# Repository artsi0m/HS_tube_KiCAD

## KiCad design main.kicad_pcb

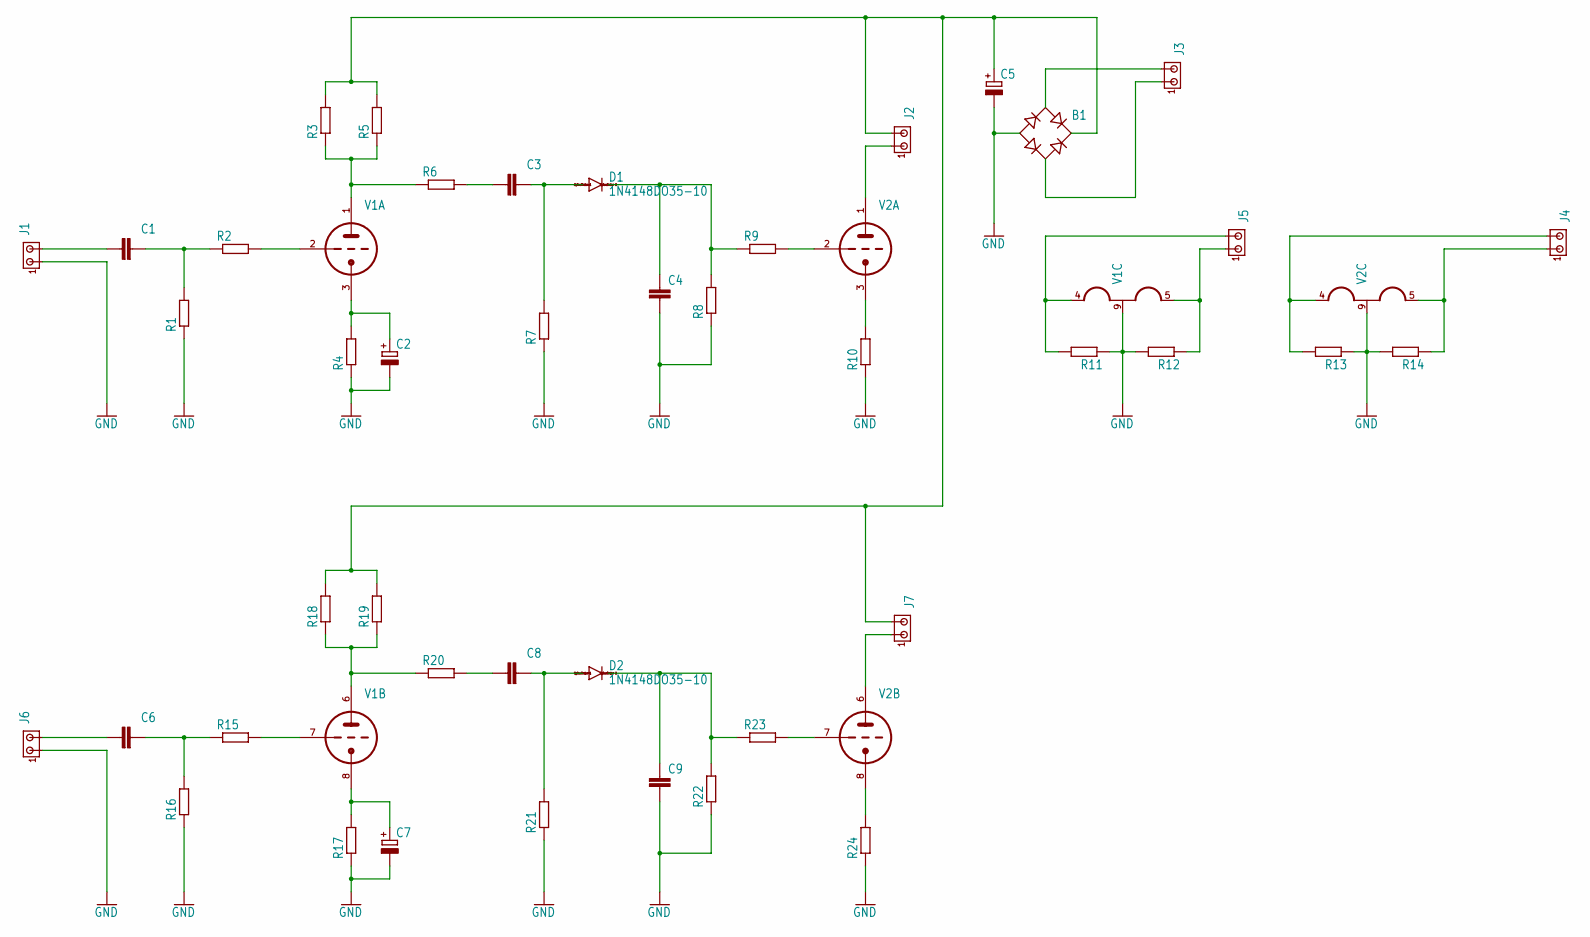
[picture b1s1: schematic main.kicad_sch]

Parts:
B1: B-DIL
C1, C3, C6, C8: C-EU225-062X268; C225-062X268
C2, C7: CPOL-EUE5-10.5; E5-10,5
C4, C9: C-EU102-064X133; C102-064X133
C5: CPOL-EUE7.5-18; E7,5-18
D1, D2: 1N4148DO35-10; DO35-10
J1, J2, J3, J4, J5, J6, J7: MTA02-156; 1X2MTA
R1, R2, R4, R6, R7, R8, R9, R10, R11, R12, R13, R14, R15, R16, R17, R20, R21, R22, R23, R24: R-EU_0207/12; 0207_12
R3, R5, R18, R19: R-EU_0309/12; 0309_12
V1, V2: 12AX7-P; TUBE

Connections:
GND: B1.-, C2.-, C4.2, C5.-, C7.-, C9.2, J1.1, J6.1, R1.1, R4.1, R7.1, R8.1, R10.1, R11.1, R12.2, R13.1, R14.2, R16.1, R17.1, R21.1, R22.1, R24.1, V1.9 (H2), V2.9 (H2)
unnamed: B1.+, C5.+, J2.2, J7.2, R3.2, R5.2, R18.2, R19.2
unnamed: B1.AC1, J3.2
unnamed: B1.AC2, J3.1
unnamed: C1.1, J1.2
unnamed: C1.2, R1.2, R2.1
unnamed: C3.1, R6.2
unnamed: C3.2, D1.A, R7.2
unnamed: C4.1, D1.C, R8.2, R9.1
unnamed: C6.1, J6.2
unnamed: C6.2, R15.1, R16.2
unnamed: C8.1, R20.2
unnamed: C8.2, D2.A, R21.2
unnamed: C9.1, D2.C, R22.2, R23.1
unnamed: R3.1, R5.1, R6.1, V1.1 (TA)
unnamed: R2.2, V1.2 (TG)
unnamed: C2.+, R4.2, V1.3 (TK)
unnamed: R18.1, R19.1, R20.1, V1.6 (TA)
unnamed: R15.2, V1.7 (TG)
unnamed: C7.+, R17.2, V1.8 (TK)
unnamed: J5.2, R11.2, V1.4 (H1)
unnamed: J5.1, R12.1, V1.5 (H3)
unnamed: J2.1, V2.1 (TA)
unnamed: R9.2, V2.2 (TG)
unnamed: R10.2, V2.3 (TK)
unnamed: J7.1, V2.6 (TA)
unnamed: R23.2, V2.7 (TG)
unnamed: R24.2, V2.8 (TK)
unnamed: J4.2, R13.2, V2.4 (H1)
unnamed: J4.1, R14.1, V2.5 (H3)

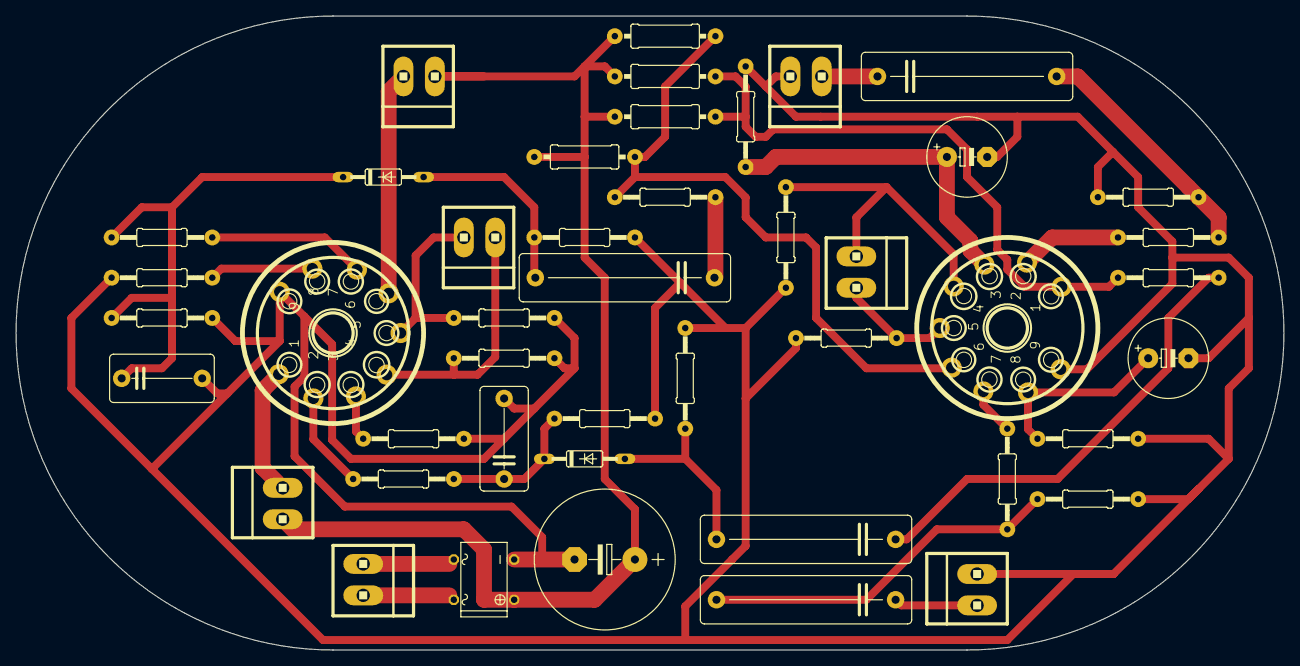
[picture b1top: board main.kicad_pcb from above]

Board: 2 copper layers, 160.0 x 80.0 mm, 45 parts (0 on the bottom side), 30 nets.

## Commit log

2024-06-25 Initial commit: Project with schematic and libs imported from Dzmitry
2024-07-03 Renamed footprints in libs to deal with error of importing to pcbdoc
2024-07-11 Made very specific edge cuts form
2024-07-11 Almost all, one connection left
2024-07-11 All parts interconnected! Only one layer used
2024-07-11 gitignore mode for emacs
2024-07-11 Trying to fix some DRC errors
2024-07-11 Исправления от Димы Орлова
2024-07-11 Диаметры у монтажных отверстий посадочных мест, -проходные дорожки
2024-07-13 pcb seems to be finished, put fabrication output in repo
2024-07-13 Seems to be finished. Grounding might be done better next time
2024-12-29 CERN Open Hardware Licence Version 2 - Permissive
2024-12-29 licence preamble
